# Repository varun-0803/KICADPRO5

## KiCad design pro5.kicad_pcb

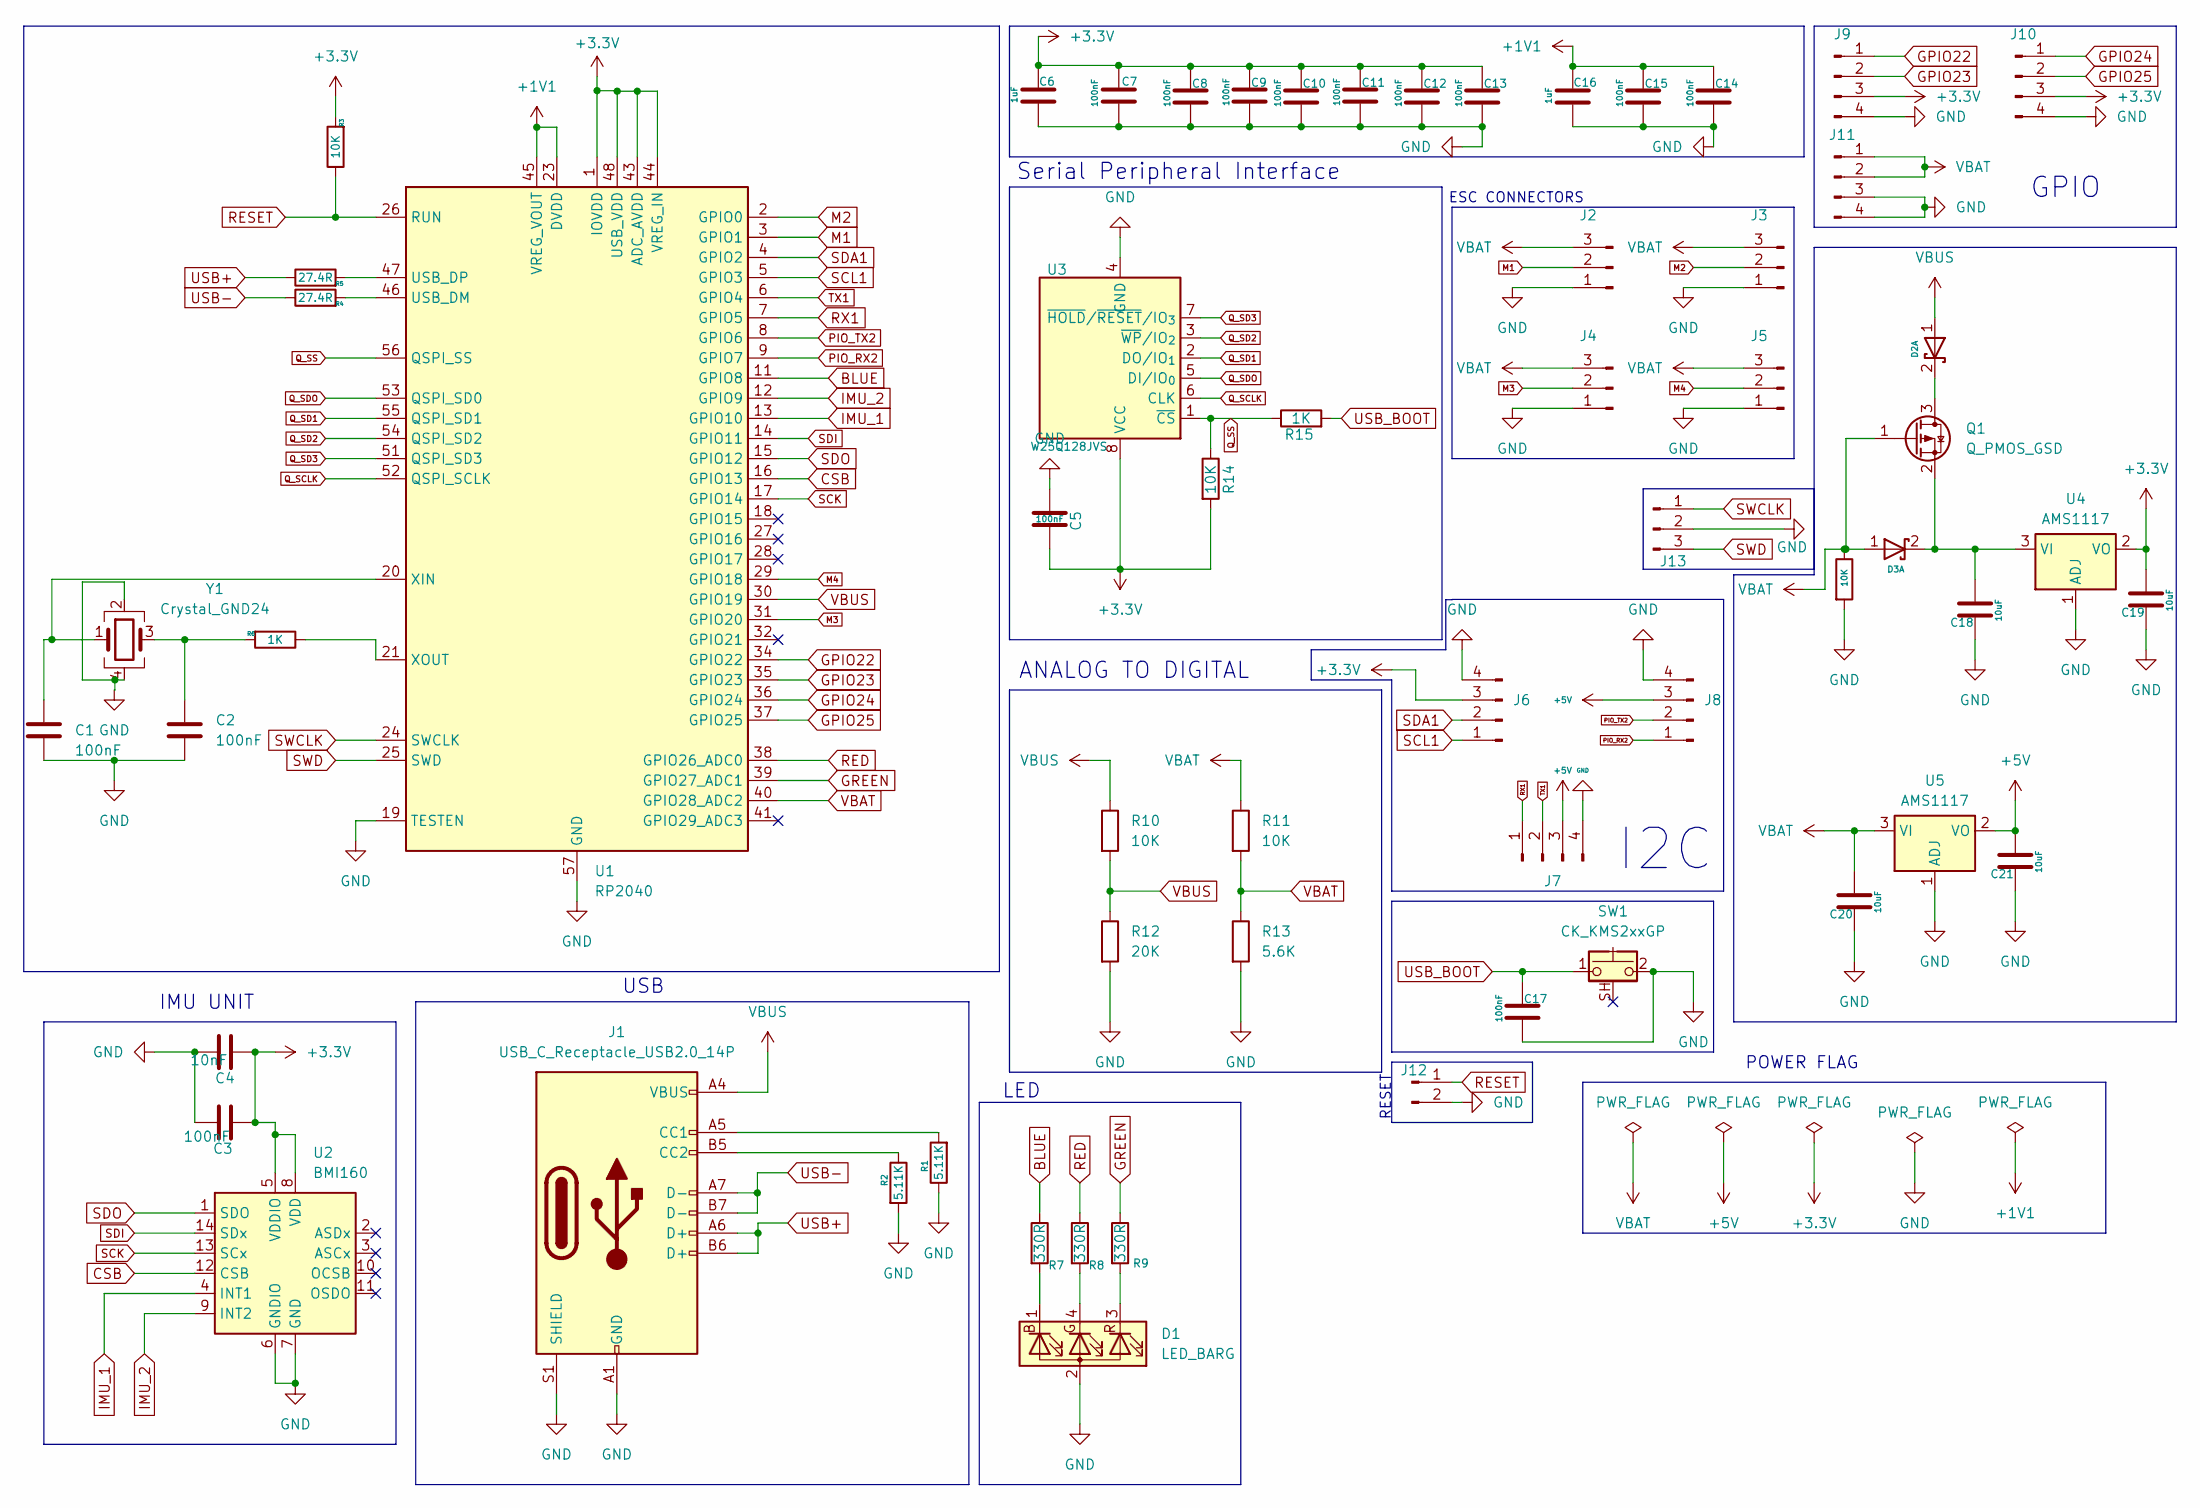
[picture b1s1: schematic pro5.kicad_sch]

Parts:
C1, C2, C3, C7, C8, C9, C10, C11, C12, C13, C14, C15, C17: 100nF; C_0201_0603Metric
C4: 10nF; C_0201_0603Metric
C5: 100nF; C_01005_0402Metric
C6, C16: 1uF; C_01005_0402Metric
C18, C19, C20, C21: 10uF; C_0805_2012Metric
D1: LED_BARG; LED_RGB_5050-6
D2, D3: D_Schottky_Dual_CommonAnode_AKK_Split; D_3220_8050Metric
J1: USB_C_Receptacle_USB2.0_14P; USB_C_Receptacle_GCT_USB4085
J2, J3, J4, J5: PinHeader_1x04_P1.00mm_Vertical
J6, J7, J8, J9, J10, J11: Conn_01x04_Pin; PinHeader_1x04_P1.00mm_Vertical
J12: Conn_01x02_Pin; PinHeader_1x02_P1.00mm_Vertical
J13: Stocko_MKS_1653-6-0-303_1x3_P2.50mm_Vertical
Q1: Q_PMOS_GSD; SOT-23
R1, R2: 5.11K; R_01005_0402Metric
R3, R10, R11, R14, R16: 10K; R_01005_0402Metric
R4, R5: 27.4R; R_01005_0402Metric
R6, R15: 1K; R_01005_0402Metric
R7, R8, R9: 330R; R_0201_0603Metric
R12: 20K; R_01005_0402Metric
R13: 5.6K; R_01005_0402Metric
SW1: CK_KMS2xxGP; SW_SPST_CK_KMS2xxGP
U1: RP2040; QFN-56-1EP_7x7mm_P0.4mm_EP3.2x3.2mm
U2: BMI160; Bosch_LGA-14_3x2.5mm_P0.5mm
U3: W25Q128JVS; SOIC-8_5.3x5.3mm_P1.27mm
U4, U5: AMS1117; SOT-223-3_TabPin2
Y1: Crystal_GND24; Crystal_SMD_0603-4Pin_6.0x3.5mm

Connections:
+1V1: C14.1, C15.1, C16.1, U1.23 (DVDD), U1.45 (VREG_VOUT), U1.50 (DVDD)
+3.3V: C3.1, C4.1, C5.2, C6.1, C7.1, C8.1, C9.1, C10.1, C11.1, C12.1, C13.1, C19.2, J6.3, J9.3, J10.3, R3.2, R14.2, U1.1 (IOVDD), U1.10 (IOVDD), U1.22 (IOVDD), U1.33 (IOVDD), U1.42 (IOVDD), U1.43 (ADC_AVDD), U1.44 (VREG_IN), U1.48 (USB_VDD), U1.49 (IOVDD), U2.5 (VDDIO), U2.8 (VDD), U3.8 (VCC), U4.2 (VO)
+5V: C21.2, J7.3, J8.3, U5.2 (VO)
BLUE: R7.1, U1.11 (GPIO8)
CSB: U1.16 (GPIO13), U2.12 (CSB); also elsewhere on the board
GND: C1.2, C2.2, C3.2, C4.2, C5.1, C6.2, C7.2, C8.2, C9.2, C10.2, C11.2, C12.2, C13.2, C14.2, C15.2, C16.2, C17.2, C18.1, C19.1, C20.1, C21.1, D1.2 (A), J1.A1 (GND), J1.A12 (GND), J1.B1 (GND), J1.B12 (GND), J1.S1 (SHIELD), J2.1, J3.1, J4.1, J5.1, J6.4, J7.4, J8.4, J9.4, J10.4, J11.3, J11.4, J12.2, J13.2, R1.1, R2.2, R12.2, R13.2, R16.2, SW1.2, U1.19 (TESTEN), U1.57 (GND), U2.6 (GNDIO), U2.7 (GND), U3.4 (GND), U4.1 (ADJ), U5.1 (ADJ), Y1.2, Y1.4
GPIO22: J9.1, U1.34 (GPIO22)
GPIO23: J9.2, U1.35 (GPIO23)
GPIO24: J10.1, U1.36 (GPIO24)
GPIO25: J10.2, U1.37 (GPIO25)
GREEN: R9.1, U1.39 (GPIO27_ADC1)
IMU_1: U1.13 (GPIO10), U2.4 (INT1)
IMU_2: U1.12 (GPIO9), U2.9 (INT2)
M1: J2.2, U1.3 (GPIO1)
M2: J3.2, U1.2 (GPIO0)
M3: J4.2, U1.31 (GPIO20)
M4: J5.2, U1.29 (GPIO18)
unnamed: C2.1, R6.2, Y1.3
unnamed: D1.1 (BK), R7.2
unnamed: D1.4 (GK), R8.2
unnamed: D1.3 (RK), R9.2
unnamed: D2.2 (K), Q1.3 (D)
unnamed: C18.2, D3.2 (K), Q1.2 (S), U4.3 (VI)
unnamed: J1.A5 (CC1), R1.2
unnamed: J1.B5 (CC2), R2.1
unnamed: R4.2, U1.46 (USB_DM)
unnamed: R5.2, U1.47 (USB_DP)
unnamed: C1.1, U1.20 (XIN), Y1.1
unnamed: R6.1, U1.21 (XOUT)
PIO_RX2: J8.1, U1.9 (GPIO7)
PIO_TX2: J8.2, U1.8 (GPIO6)
Q_SCLK: U1.52 (QSPI_SCLK), U3.6 (CLK)
Q_SD1: U1.55 (QSPI_SD1), U3.2 (DO/IO_{1})
Q_SD2: U1.54 (QSPI_SD2), U3.3 (~WP/IO_{2})
Q_SD3: U1.51 (QSPI_SD3), U3.7 (~HOLD/~RESET/IO_{3})
Q_SDO: U1.53 (QSPI_SD0), U3.5 (DI/IO_{0})
Q_SS: R14.1, R15.1, U1.56 (QSPI_SS), U3.1 (~CS)
RED: R8.1, U1.38 (GPIO26_ADC0)
RESET: J12.1, R3.1, U1.26 (RUN)
RX1: J7.1, U1.7 (GPIO5)
SCK: U1.17 (GPIO14), U2.13 (SCx); also elsewhere on the board
SCL1: J6.1, U1.5 (GPIO3)
SDA1: J6.2, U1.4 (GPIO2)
SDI: U1.14 (GPIO11), U2.14 (SDx); also elsewhere on the board
SDO: U1.15 (GPIO12), U2.1 (SDO); also elsewhere on the board
SWCLK: J13.1, U1.24 (SWCLK)
SWD: J13.3, U1.25 (SWD)
TX1: J7.2, U1.6 (GPIO4)
USB+: J1.A6 (D+), J1.B6 (D+), R5.1
USB-: J1.A7 (D-), J1.B7 (D-), R4.1
USB_BOOT: C17.1, R15.2, SW1.1
VBAT: C20.2, D3.1 (A), J2.3, J3.3, J4.3, J5.3, J11.1, J11.2, Q1.1 (G), R11.1, R11.2, R13.1, R16.1, U1.40 (GPIO28_ADC2), U5.3 (VI)
VBUS: D2.1 (A), J1.A4 (VBUS), J1.A9 (VBUS), J1.B4 (VBUS), J1.B9 (VBUS), R10.1, R10.2, R12.1, U1.30 (GPIO19)

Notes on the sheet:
ANALOG TO DIGITAL
ESC CONNECTORS
Serial Peripheral Interface
USB
GPIO
LED
POWER FLAG
IMU UNIT
I2C
RESET

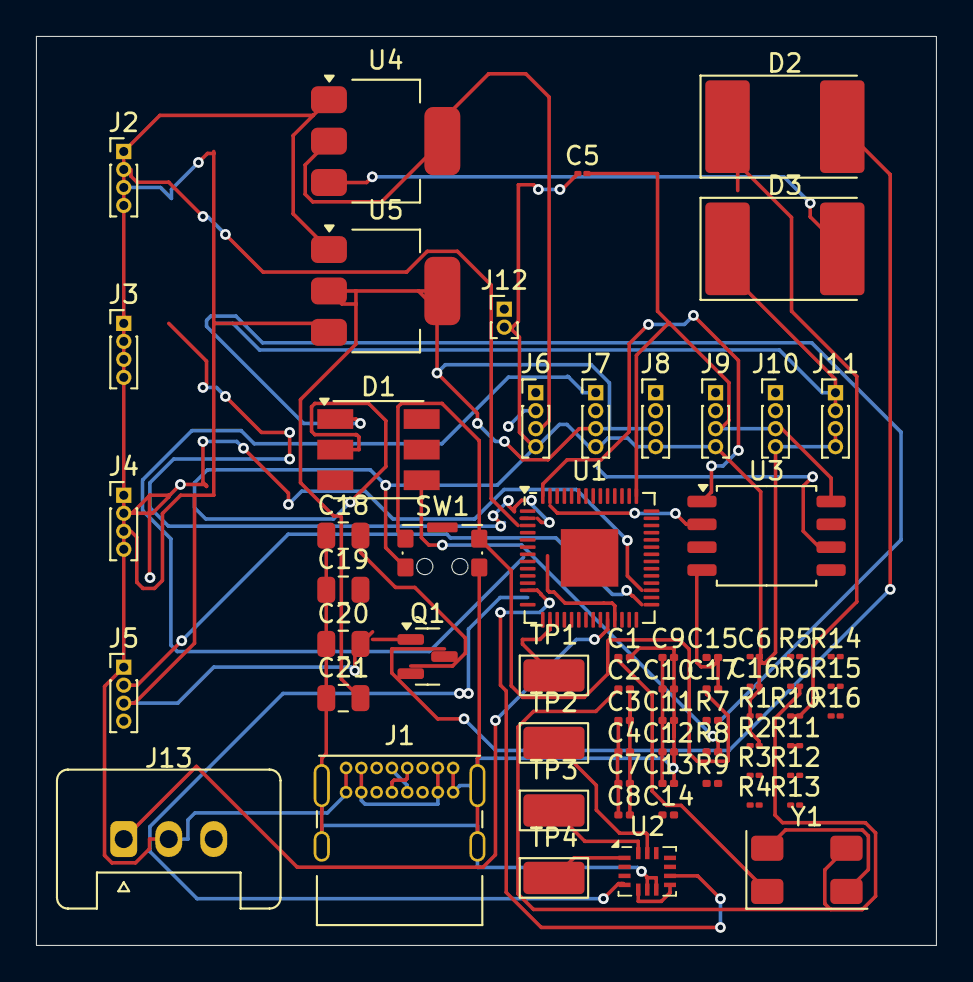
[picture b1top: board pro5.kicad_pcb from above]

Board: 2 copper layers, 50.0 x 50.5 mm, 65 parts (0 on the bottom side), 53 nets.

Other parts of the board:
TP1, TP2, TP3, TP4: TestPoint; TestPoint_Keystone_5015_Micro_Mini

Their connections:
CSB: TP1.1; also elsewhere on the board
SCK: TP2.1; also elsewhere on the board
SDI: TP3.1; also elsewhere on the board
SDO: TP4.1; also elsewhere on the board

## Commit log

2025-06-16 Add KiCad project files for KICADPRO5
